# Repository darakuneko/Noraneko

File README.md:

# Noraneko Project
Noraneko Project is an open source keyboard project.

## License
Coffee License [en](/LICENSE) / [ja](/LICENSE_JA)

☕️☕️☕️ Donation ☕️☕️☕️   
[Amazon](https://www.amazon.co.jp/hz/wishlist/ls/66VQJTRHISQT) or [Ko-fi](https://ko-fi.com/darakuneko)  

If you did sell or modify them, please let us know.

As the author, I would be very happy if you would do so.

Also if you have any questions, [please contact me](https://twitter.com/daraku__neko).

## Why is it not wired?
I want to see a variety of wires on one keyboard.

It makes for good wiring practice.

If wired, pull request kicad_pcb file under each data.

example: [wired](./noraneko42c/v1.0/pcb/wired/)  
/{keyboard}/.../pcb/wired/{username}/ 

### Wiring Engineer
[blackout](https://github.com/blackout157w) - [Noraneko52R v1.0](https://github.com/darakuneko/Noraneko/tree/main/noraneko52r/v1.0/pcb/wired/blackout)

## About Plate Data
I only have data for elecrow.

If you have created data for other stores, please make a pull request.

/{keyboard}/.../plate/{shop}/

## About Noraneko Symbol & Footprint
base on geek-rabb1t's Symbol & Footprint.

https://github.com/geek-rabb1t/keyboard_footprint

## Noraneko42C
Column Staggered Layout Keyboard.

## Noraneko52R
Row Staggered Layout Keyboard.

## Noraneko42W
Willow Layout Keyboard.

# Noraneko42L
Lotus Layout Keyboard.

# Noraneko42GR
Grin Layout Keyboard.

# Noraneko42A
Alice Layout Keyboard.

# Noraneko42SGR
Sagittarius Layout Keyboard.

# Noraneko42UZU  
Uzu Layout Keyboard.

# Noraneko42O
Ortholinear Layout Keyboard.

# Noraneko43TS
Symmetric staggered Layout (Treadstone Layout) keyboard.

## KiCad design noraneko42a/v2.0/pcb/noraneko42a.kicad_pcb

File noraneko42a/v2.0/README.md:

# Noraneko42A  

The Noraneko42A is 42key Alice keyboard.  

## Parts  

Top plate --- 1 pc  
Middle plate --- 1 pc   
Main FR4 plate --- 1 pc  
Bottom1 plate --- 1 pc    
Bottom2 plate --- 1 pc  
M2 spacer 3mm --- 9 pcs  
M2 screw 3mm --- 18 pcs  (Screw heads should be 2 mm or less）  
RP2040-Zero --- 1 pc   
1N4148W --- 42 pcs   
SK6812MINI-E --- 42 pcs  
MX key switch --- 42 pcs   
MX keycap 1U --- 35 pcs  
MX keycap 1.25U --- 2 pcs  
MX keycap 1.75U --- 3 pcs  
MX keycap 2U --- 2 pcs  

Bumpon --- Any quantity 

## Firmware

Firmware
[v2.0](https://github.com/darakuneko/Noraneko/raw/main/noraneko42a/v2.0/firmware/noraneko42a_vial.uf2)  
Check if the firmware can write to RP2040-Zero.  
Download the firmware.   
Connect while holding down the Boot button.  
RPI-RP2 will appear.  
Copy the downloaded firmware to RPI-RP2.  
Make sure that Noraneko42A is connected to your PC.    
[Vial Support](https://get.vial.today/)  

## Soldering

RP2040-Zero(SMD),diodes, LEDs, and sockets.  
Be careful of the direction of soldering.  
But Resistors has no polarity.

## Build
This includes photos of other keyboards as well, but the assembly method is the same.

Install spacers, screws, and Bumpon on bottom plate and main plate.
Put on the switches and keycaps and you're done.

## Completed!!

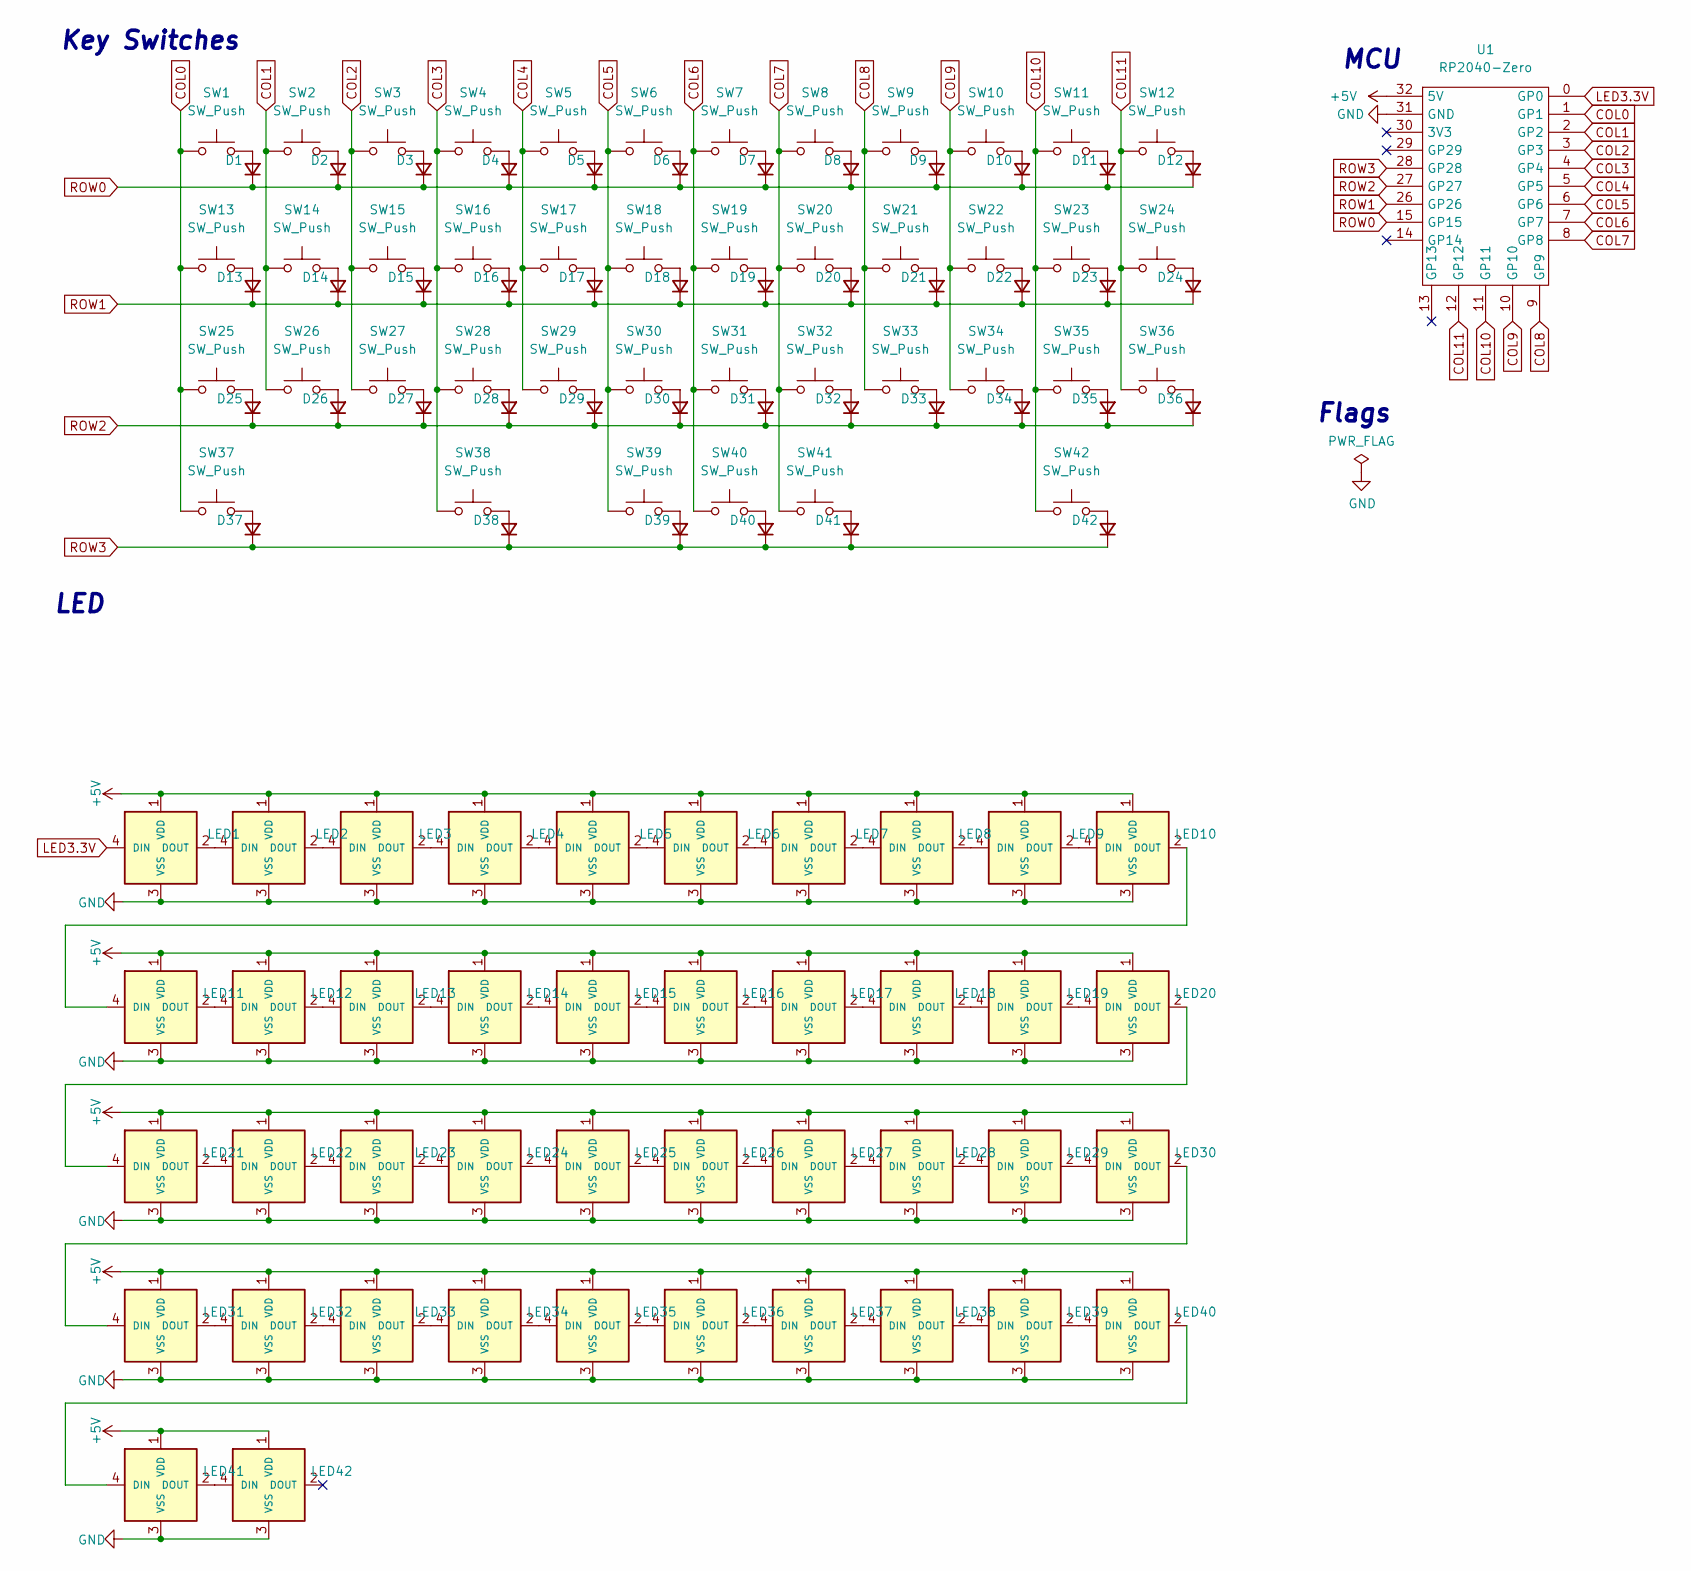
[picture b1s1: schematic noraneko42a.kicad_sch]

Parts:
D1, D2, D3, D4, D5, D6, D7, D8, D9, D10, D11, D12, D13, D14, D15, D16, D17, D18, D19, D20, D21, D22, D23, D24, D25, D26, D27, D28, D29, D30, D31, D32, D33, D34, D35, D36, D37, D38, D39, D40, D41, D42: D; 1N4148W; LCSC C81598
LED1, LED2, LED3, LED4, LED5, LED6, LED7, LED8, LED9, LED10, LED11, LED12, LED13, LED14, LED15, LED16, LED17, LED18, LED19, LED20, LED21, LED22, LED23, LED24, LED25, LED26, LED27, LED28, LED29, LED30, LED31, LED32, LED33, LED34, LED35, LED36, LED37, LED38, LED39, LED40, LED41, LED42: SK6812MINI-E; LCSC C5378731
SW1, SW2, SW3, SW4, SW5, SW6, SW7, SW8, SW9, SW10, SW11, SW12, SW14, SW15, SW16, SW17, SW18, SW19, SW20, SW21, SW22, SW23, SW24, SW26, SW27, SW28, SW29, SW30, SW31, SW32, SW33, SW34, SW35, SW39, SW40: SW_Push; MX_Socket; LCSC C49352235
SW13, SW36, SW37, SW42: SW_Push; MX_Socket_1.25U; LCSC C49352235
SW25: SW_Push; MX_Socket_1.75U; LCSC C49352235
SW38, SW41: SW_Push; MX_Socket_2.0U; LCSC C49352235
U1: RP2040-Zero; RP2040-Zero-SMD

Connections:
+5V: LED1.1 (VDD), LED2.1 (VDD), LED3.1 (VDD), LED4.1 (VDD), LED5.1 (VDD), LED6.1 (VDD), LED7.1 (VDD), LED8.1 (VDD), LED9.1 (VDD), LED10.1 (VDD), LED11.1 (VDD), LED12.1 (VDD), LED13.1 (VDD), LED14.1 (VDD), LED15.1 (VDD), LED16.1 (VDD), LED17.1 (VDD), LED18.1 (VDD), LED19.1 (VDD), LED20.1 (VDD), LED21.1 (VDD), LED22.1 (VDD), LED23.1 (VDD), LED24.1 (VDD), LED25.1 (VDD), LED26.1 (VDD), LED27.1 (VDD), LED28.1 (VDD), LED29.1 (VDD), LED30.1 (VDD), LED31.1 (VDD), LED32.1 (VDD), LED33.1 (VDD), LED34.1 (VDD), LED35.1 (VDD), LED36.1 (VDD), LED37.1 (VDD), LED38.1 (VDD), LED39.1 (VDD), LED40.1 (VDD), LED41.1 (VDD), LED42.1 (VDD), U1.32 (5V)
COL0: SW1.1, SW13.1, SW25.1, SW37.1, U1.1 (GP1)
COL1: SW2.1, SW14.1, SW26.1, U1.2 (GP2)
COL2: SW3.1, SW15.1, SW27.1, U1.3 (GP3)
COL3: SW4.1, SW16.1, SW28.1, SW38.1, U1.4 (GP4)
COL4: SW5.1, SW17.1, SW29.1, U1.5 (GP5)
COL5: SW6.1, SW18.1, SW30.1, SW39.1, U1.6 (GP6)
COL6: SW7.1, SW19.1, SW31.1, SW40.1, U1.7 (GP7)
COL7: SW8.1, SW20.1, SW32.1, SW41.1, U1.8 (GP8)
COL8: SW9.1, SW21.1, SW33.1, U1.9 (GP9)
COL9: SW10.1, SW22.1, SW34.1, U1.10 (GP10)
COL10: SW11.1, SW23.1, SW35.1, SW42.1, U1.11 (GP11)
COL11: SW12.1, SW24.1, SW36.1, U1.12 (GP12)
GND: LED1.3 (VSS), LED2.3 (VSS), LED3.3 (VSS), LED4.3 (VSS), LED5.3 (VSS), LED6.3 (VSS), LED7.3 (VSS), LED8.3 (VSS), LED9.3 (VSS), LED10.3 (VSS), LED11.3 (VSS), LED12.3 (VSS), LED13.3 (VSS), LED14.3 (VSS), LED15.3 (VSS), LED16.3 (VSS), LED17.3 (VSS), LED18.3 (VSS), LED19.3 (VSS), LED20.3 (VSS), LED21.3 (VSS), LED22.3 (VSS), LED23.3 (VSS), LED24.3 (VSS), LED25.3 (VSS), LED26.3 (VSS), LED27.3 (VSS), LED28.3 (VSS), LED29.3 (VSS), LED30.3 (VSS), LED31.3 (VSS), LED32.3 (VSS), LED33.3 (VSS), LED34.3 (VSS), LED35.3 (VSS), LED36.3 (VSS), LED37.3 (VSS), LED38.3 (VSS), LED39.3 (VSS), LED40.3 (VSS), LED41.3 (VSS), LED42.3 (VSS), U1.31 (GND)
LED3.3V: LED1.4 (DIN), U1.0 (GP0)
unnamed: D1.2 (A), SW1.2
unnamed: D2.2 (A), SW2.2
unnamed: D3.2 (A), SW3.2
unnamed: D4.2 (A), SW4.2
unnamed: D5.2 (A), SW5.2
unnamed: D6.2 (A), SW6.2
unnamed: D7.2 (A), SW7.2
unnamed: D8.2 (A), SW8.2
unnamed: D9.2 (A), SW9.2
unnamed: D10.2 (A), SW10.2
unnamed: D11.2 (A), SW11.2
unnamed: D12.2 (A), SW12.2
unnamed: D13.2 (A), SW13.2
unnamed: D14.2 (A), SW14.2
unnamed: D15.2 (A), SW15.2
unnamed: D16.2 (A), SW16.2
unnamed: D17.2 (A), SW17.2
unnamed: D18.2 (A), SW18.2
unnamed: D19.2 (A), SW19.2
unnamed: D20.2 (A), SW20.2
unnamed: D21.2 (A), SW21.2
unnamed: D22.2 (A), SW22.2
unnamed: D23.2 (A), SW23.2
unnamed: D24.2 (A), SW24.2
unnamed: D25.2 (A), SW25.2
unnamed: D26.2 (A), SW26.2
unnamed: D27.2 (A), SW27.2
unnamed: D28.2 (A), SW28.2
unnamed: D29.2 (A), SW29.2
unnamed: D30.2 (A), SW30.2
unnamed: D31.2 (A), SW31.2
unnamed: D32.2 (A), SW32.2
unnamed: D33.2 (A), SW33.2
unnamed: D34.2 (A), SW34.2
unnamed: D35.2 (A), SW35.2
unnamed: D36.2 (A), SW36.2
unnamed: D37.2 (A), SW37.2
unnamed: D38.2 (A), SW38.2
unnamed: D39.2 (A), SW39.2
unnamed: D40.2 (A), SW40.2
unnamed: D41.2 (A), SW41.2
unnamed: D42.2 (A), SW42.2
unnamed: LED1.2 (DOUT), LED2.4 (DIN)
unnamed: LED2.2 (DOUT), LED3.4 (DIN)
unnamed: LED3.2 (DOUT), LED4.4 (DIN)
unnamed: LED4.2 (DOUT), LED5.4 (DIN)
unnamed: LED5.2 (DOUT), LED6.4 (DIN)
unnamed: LED6.2 (DOUT), LED7.4 (DIN)
unnamed: LED7.2 (DOUT), LED8.4 (DIN)
unnamed: LED8.2 (DOUT), LED9.4 (DIN)
unnamed: LED9.2 (DOUT), LED10.4 (DIN)
unnamed: LED10.2 (DOUT), LED11.4 (DIN)
unnamed: LED11.2 (DOUT), LED12.4 (DIN)
unnamed: LED12.2 (DOUT), LED13.4 (DIN)
unnamed: LED13.2 (DOUT), LED14.4 (DIN)
unnamed: LED14.2 (DOUT), LED15.4 (DIN)
unnamed: LED15.2 (DOUT), LED16.4 (DIN)
unnamed: LED16.2 (DOUT), LED17.4 (DIN)
unnamed: LED17.2 (DOUT), LED18.4 (DIN)
unnamed: LED18.2 (DOUT), LED19.4 (DIN)
unnamed: LED19.2 (DOUT), LED20.4 (DIN)
unnamed: LED20.2 (DOUT), LED21.4 (DIN)
unnamed: LED21.2 (DOUT), LED22.4 (DIN)
unnamed: LED22.2 (DOUT), LED23.4 (DIN)
unnamed: LED23.2 (DOUT), LED24.4 (DIN)
unnamed: LED24.2 (DOUT), LED25.4 (DIN)
unnamed: LED25.2 (DOUT), LED26.4 (DIN)
unnamed: LED26.2 (DOUT), LED27.4 (DIN)
unnamed: LED27.2 (DOUT), LED28.4 (DIN)
unnamed: LED28.2 (DOUT), LED29.4 (DIN)
unnamed: LED29.2 (DOUT), LED30.4 (DIN)
unnamed: LED30.2 (DOUT), LED31.4 (DIN)
unnamed: LED31.2 (DOUT), LED32.4 (DIN)
unnamed: LED32.2 (DOUT), LED33.4 (DIN)
unnamed: LED33.2 (DOUT), LED34.4 (DIN)
unnamed: LED34.2 (DOUT), LED35.4 (DIN)
unnamed: LED35.2 (DOUT), LED36.4 (DIN)
unnamed: LED36.2 (DOUT), LED37.4 (DIN)
unnamed: LED37.2 (DOUT), LED38.4 (DIN)
unnamed: LED38.2 (DOUT), LED39.4 (DIN)
unnamed: LED39.2 (DOUT), LED40.4 (DIN)
unnamed: LED40.2 (DOUT), LED41.4 (DIN)
unnamed: LED41.2 (DOUT), LED42.4 (DIN)
ROW0: D1.1 (K), D2.1 (K), D3.1 (K), D4.1 (K), D5.1 (K), D6.1 (K), D7.1 (K), D8.1 (K), D9.1 (K), D10.1 (K), D11.1 (K), D12.1 (K), U1.15 (GP15)
ROW1: D13.1 (K), D14.1 (K), D15.1 (K), D16.1 (K), D17.1 (K), D18.1 (K), D19.1 (K), D20.1 (K), D21.1 (K), D22.1 (K), D23.1 (K), D24.1 (K), U1.26 (GP26)
ROW2: D25.1 (K), D26.1 (K), D27.1 (K), D28.1 (K), D29.1 (K), D30.1 (K), D31.1 (K), D32.1 (K), D33.1 (K), D34.1 (K), D35.1 (K), D36.1 (K), U1.27 (GP27)
ROW3: D37.1 (K), D38.1 (K), D39.1 (K), D40.1 (K), D41.1 (K), D42.1 (K), U1.28 (GP28)

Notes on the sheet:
MCU
LED
Flags
Key Switches

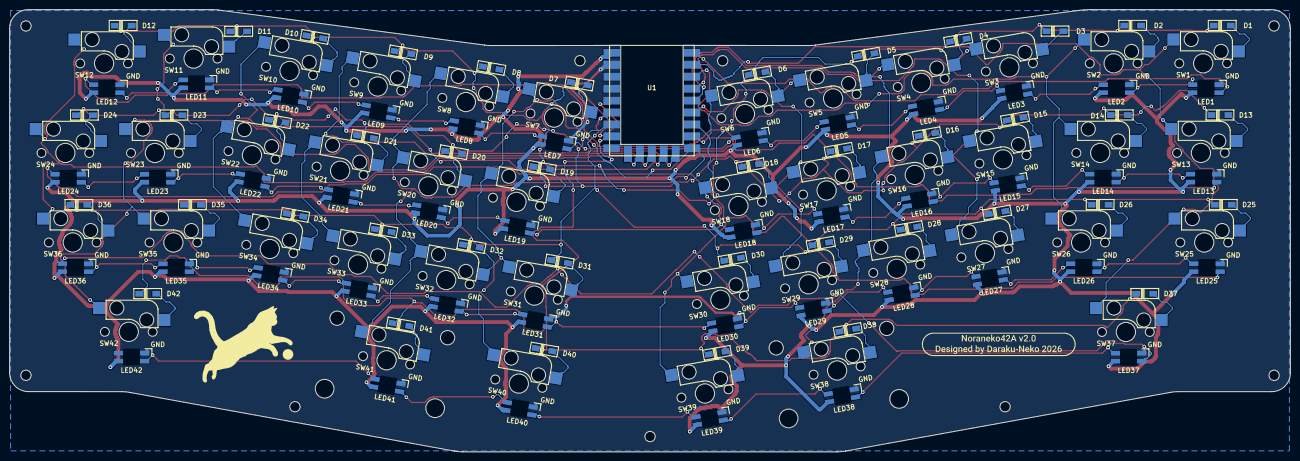
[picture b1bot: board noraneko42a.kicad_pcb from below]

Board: 2 copper layers, 272.5 x 94.1 mm, 128 parts (86 on the bottom side), 102 nets.

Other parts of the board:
tlg_Roboto_MediumNoraneko42A v20: G***; tlg_Roboto_MediumNoraneko42A v20

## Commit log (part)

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2022-10-10 Create LICENSE
2022-10-10 Create LICENSE_JA
2022-10-10 add: logo
2022-10-10 add: noraneko42c
2022-10-10 minor bugs fixs
2022-10-10 Add wired file from freerouting
2022-10-15 Update LICENSE
2022-10-15 Update LICENSE_JA
2022-10-18 Add Firmware
2022-10-18 Update Noraneko42C Source
2022-10-29 Update Noraneko42c Silk
2022-11-11 Update Noraneko52R
2022-11-11 Add Noraneko52R firmware
2022-11-14 Fix Noraneko52R LED Position
2022-11-15 Fix Noraneko52R layer count
2022-11-25 fix: chconf to prevent freezes
2023-01-30 noraneko52r blackout ver.
    PCB&plate
2023-03-03 add: Noraneko52R v1.1
2023-04-25 add: Noraneko42W Firmware
2023-04-25 add: Noraneko42W PCB,Plate
2023-05-05 add: Noraneko42L
2023-09-18 add: Noraneko52R Vial
2023-09-23 add: Noraneko42C v2.0 firmware
2023-09-25 add: Noraneko42C v2 PCB/Plate
2023-10-27 add: noraneko42gr
2023-11-09 fix: led settings
2023-11-11 add: noraneko42gr v1.1
2023-11-11 Revert "Update README.md"
    This reverts commit ad64ae54695b70055db23a954434a2934dfb23a8.
2023-11-11 fix: keymap
2023-12-06 fix: noraneko52 v1.0 firmware link
2023-12-12 update: Noraneko42GR layer color
2023-12-13 remove: mac files
2023-12-13 fix: noraneko42gr vial json
2023-12-26 add: noraneko42a firmware
2024-02-24 add: 42gr v1.2 and 42a pcb
2024-03-30 add: 42C v2.1 firmware
2024-06-01 add: noraneko42w v1.1
2024-06-01 fix: doc
2024-06-30 add: 42l v1.1 firmware
2024-08-26 fix:42c firmware
2024-08-26 add: 42c v2.1 pcb
2024-08-26 add: 42sgr
2024-08-26 add: 42sgr readme
2024-11-24 Update noraneko42uzu config.h, keyboard.json, keymap.c, and 28 more files
2024-11-25 add: 42uzu readme
2025-02-12 add: Noraneko42O
2025-03-14 Update noraneko43ts.zip, noraneko43ts_vial.uf2, 1N4148W.kicad_mod, and 22 more files
2025-03-14 add: README
